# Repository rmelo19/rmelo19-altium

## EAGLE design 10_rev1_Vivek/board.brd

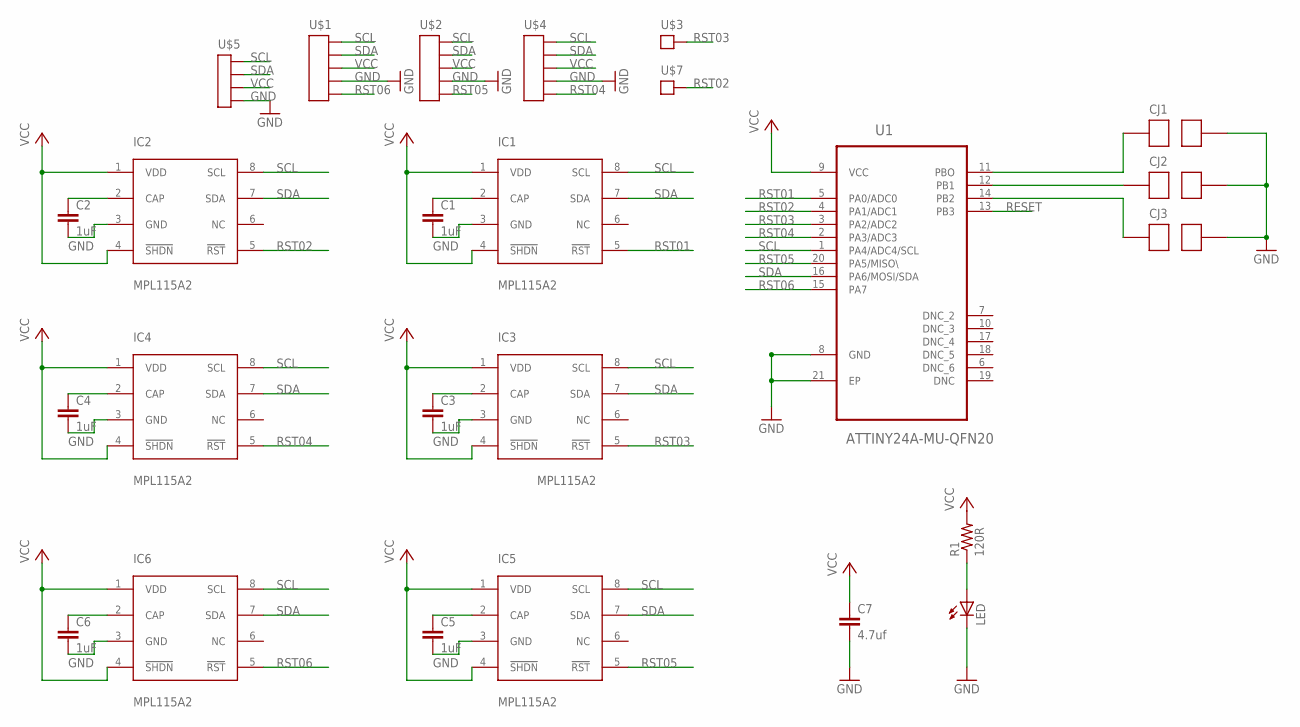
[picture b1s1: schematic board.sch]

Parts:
C1, C2, C3, C4, C5, C6: 1uF; C0402
C7: 4.7uf; C0402
CJ1, CJ2, CJ3: 2_P
IC1, IC2, IC3, IC4, IC5, IC6: MPL115A2
LED: LEDSML0603; SML0603
R1: 120R; R0402
U1: ATTINY24A-MU-QFN20; QFN50P400X400X80-21N
U$1, U$2, U$4: 5_PIN_CON
U$3, U$7: 1_PIN_CON
U$5: 4_PIN_CON

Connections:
GND: C1.2, C2.2, C3.2, C4.2, C5.2, C6.2, C7.2, CJ1.P$2, CJ2.P$2, CJ3.P$2, IC1.3 (GND), IC2.3 (GND), IC3.3 (GND), IC4.3 (GND), IC5.3 (GND), IC6.3 (GND), LED.C, U1.8 (GND), U1.21 (EP), U$1.4 (GND), U$2.4 (GND), U$4.4 (GND), U$5.4 (GND)
unnamed: C1.1, IC1.2 (CAP)
unnamed: C5.1, IC5.2 (CAP)
unnamed: C2.1, IC2.2 (CAP)
unnamed: C6.1, IC6.2 (CAP)
unnamed: C3.1, IC3.2 (CAP)
unnamed: CJ3.P$1, U1.14 (PB2)
unnamed: C4.1, IC4.2 (CAP)
unnamed: CJ2.P$1, U1.12 (PB1)
unnamed: CJ1.P$1, U1.11 (PBO)
unnamed: LED.A, R1.1
RESET: U1.13 (PB3)
RST01: IC1.5 (!RST), U1.5 (PA0/ADC0)
RST02: IC2.5 (!RST), U1.4 (PA1/ADC1), U$7.1
RST03: IC3.5 (!RST), U1.3 (PA2/ADC2), U$3.1
RST04: IC4.5 (!RST), U1.2 (PA3/ADC3), U$4.5 (RST)
RST05: IC5.5 (!RST), U1.20 (PA5/MISO\), U$2.5 (RST)
RST06: IC6.5 (!RST), U1.15 (PA7), U$1.5 (RST)
SCL: IC1.8 (SCL), IC2.8 (SCL), IC3.8 (SCL), IC4.8 (SCL), IC5.8 (SCL), IC6.8 (SCL), U1.1 (PA4/ADC4/SCL), U$1.1 (CLK), U$2.1 (CLK), U$4.1 (CLK), U$5.1 (CLK)
SDA: IC1.7 (SDA), IC2.7 (SDA), IC3.7 (SDA), IC4.7 (SDA), IC5.7 (SDA), IC6.7 (SDA), U1.16 (PA6/MOSI/SDA), U$1.2 (DATA), U$2.2 (DATA), U$4.2 (DATA), U$5.2 (DATA)
VCC: C7.1, IC1.1 (VDD), IC1.4 (!SHDN), IC2.1 (VDD), IC2.4 (!SHDN), IC3.1 (VDD), IC3.4 (!SHDN), IC4.1 (VDD), IC4.4 (!SHDN), IC5.1 (VDD), IC5.4 (!SHDN), IC6.1 (VDD), IC6.4 (!SHDN), R1.2, U1.9 (VCC), U$1.3 (VCC), U$2.3 (VCC), U$4.3 (VCC), U$5.3 (VCC)

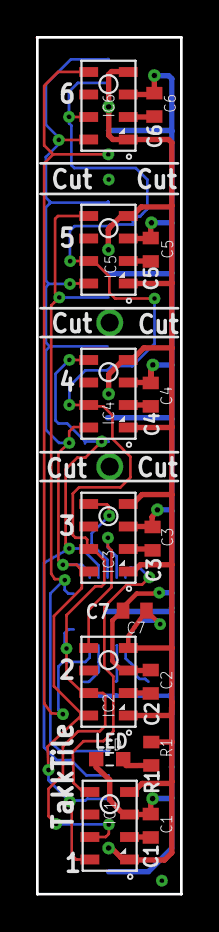
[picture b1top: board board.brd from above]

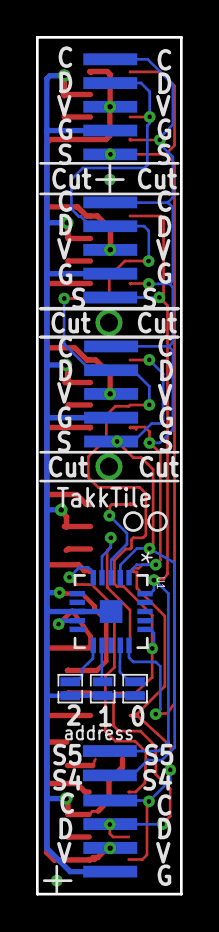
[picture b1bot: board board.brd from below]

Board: 2 copper layers, 8.0 x 47.6 mm, 25 parts (10 on the bottom side), 20 nets.

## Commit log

2016-06-21 initial work
2016-06-22 more adjusts
2016-06-24 updates on sensor board
2016-07-13 Proximal boards, commented some components in the library, SeeedStudio Design Rules
2016-07-15 altium files board, libraries, ... from laptop
2016-07-15 updates to proximal
2016-07-15 distal
2016-07-15 changes on distal
2016-07-16 merging files and organizing library
